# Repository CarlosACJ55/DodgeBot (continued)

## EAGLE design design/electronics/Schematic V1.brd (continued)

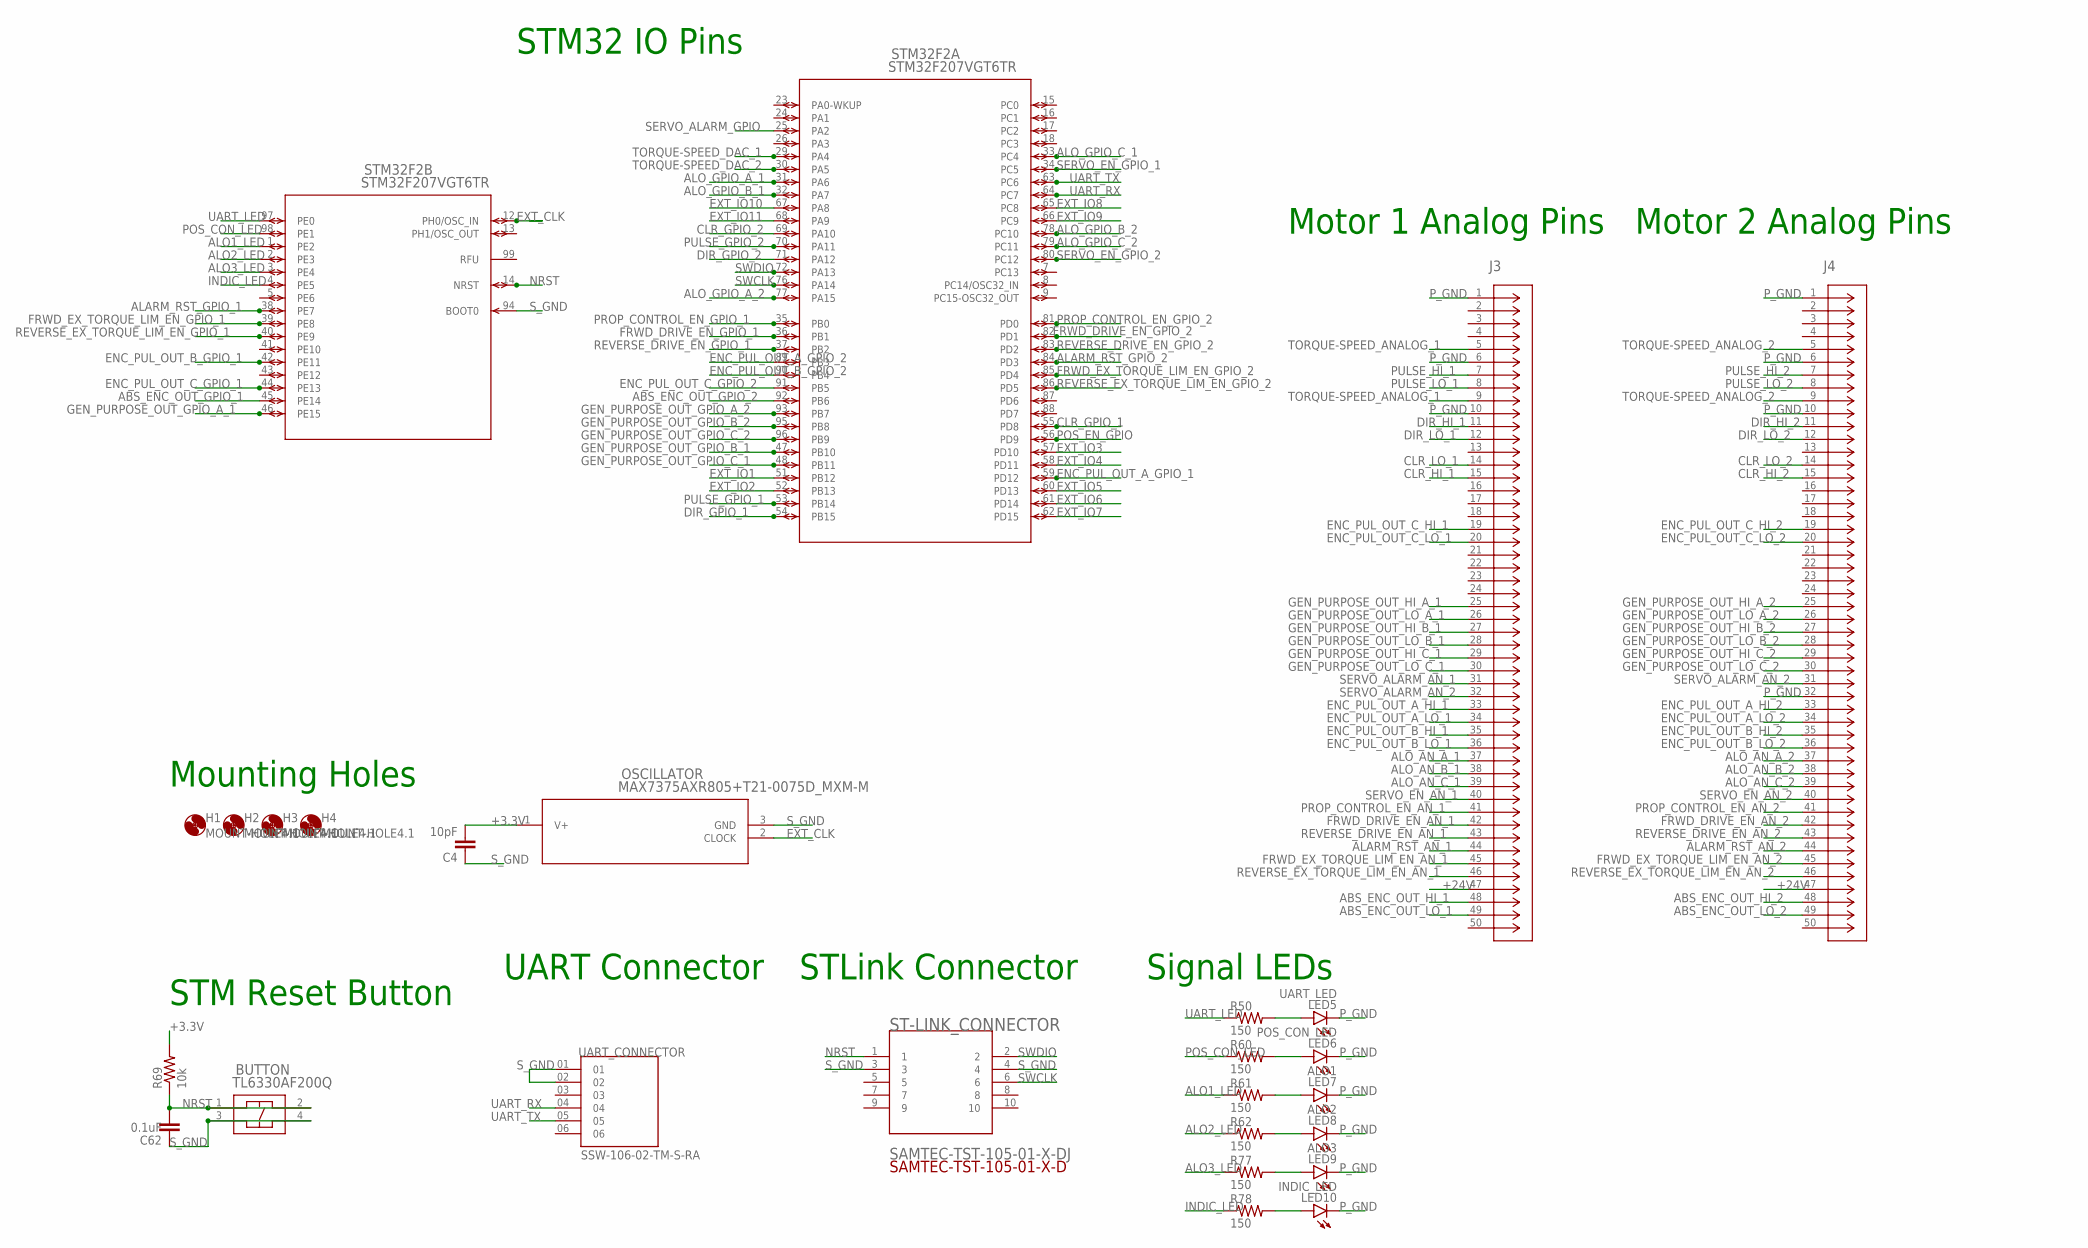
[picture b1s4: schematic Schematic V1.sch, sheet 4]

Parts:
BUTTON: TL6330AF200Q; TL6330_EWI
C4: 10pF; 0805
C62: 0.1uF; 0805
H1, H2, H3, H4: MOUNT-HOLE4.1; 4,1
J3, J4: DD50P564GTXLF; CONN_DD50P564GTXLF_AMP
LED5: UART_LED; CHIPLED_0805
LED6: POS_CON_LED; CHIPLED_0805
LED7: ALO1; CHIPLED_0805
LED8: ALO2; CHIPLED_0805
LED9: ALO3; CHIPLED_0805
LED10: INDIC_LED; CHIPLED_0805
OSCILLATOR: MAX7375AXR805+T21-0075D_MXM-M; 21-0075D_MXM-M
R50, R60, R61, R62, R77, R78: 150; R0805
R69: 10k; R0805
ST-LINK_CONNECTOR: SAMTEC-TST-105-01-X-DJ; SAMTEC-TST-105-01-X-D
STM32F2: STM32F207VGT6TR; LQFP100-14X14MM
UART_CONNECTOR: SSW-106-02-TM-S-RA; SAMTEC_SSW-106-02-TM-S-RA

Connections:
+3.3V: C4.2, OSCILLATOR.1 (V+), R69.2; also elsewhere on the board
+24V: J3.47, J4.47; also elsewhere on the board
ABS_ENC_OUT_GPIO_1: STM32F2.45 (PE14); also elsewhere on the board
ABS_ENC_OUT_GPIO_2: STM32F2.92 (PB6); also elsewhere on the board
ABS_ENC_OUT_HI_1: J3.48; also elsewhere on the board
ABS_ENC_OUT_HI_2: J4.48; also elsewhere on the board
ABS_ENC_OUT_LO_1: J3.49; also elsewhere on the board
ABS_ENC_OUT_LO_2: J4.49; also elsewhere on the board
ALARM_RST_AN_1: J3.44; also elsewhere on the board
ALARM_RST_AN_2: J4.44; also elsewhere on the board
ALARM_RST_GPIO_1: STM32F2.38 (PE7); also elsewhere on the board
ALARM_RST_GPIO_2: STM32F2.84 (PD3); also elsewhere on the board
ALO1_LED: R61.1, STM32F2.1 (PE2)
ALO2_LED: R62.1, STM32F2.2 (PE3)
ALO3_LED: R77.1, STM32F2.3 (PE4)
ALO_AN_A_1: J3.37; also elsewhere on the board
ALO_AN_A_2: J4.37; also elsewhere on the board
ALO_AN_B_1: J3.38; also elsewhere on the board
ALO_AN_B_2: J4.38; also elsewhere on the board
ALO_AN_C_1: J3.39; also elsewhere on the board
ALO_AN_C_2: J4.39; also elsewhere on the board
ALO_GPIO_A_1: STM32F2.31 (PA6); also elsewhere on the board
ALO_GPIO_A_2: STM32F2.77 (PA15); also elsewhere on the board
ALO_GPIO_B_1: STM32F2.32 (PA7); also elsewhere on the board
ALO_GPIO_B_2: STM32F2.78 (PC10); also elsewhere on the board
ALO_GPIO_C_1: STM32F2.33 (PC4); also elsewhere on the board
ALO_GPIO_C_2: STM32F2.79 (PC11); also elsewhere on the board
CLR_GPIO_1: STM32F2.55 (PD8); also elsewhere on the board
CLR_GPIO_2: STM32F2.69 (PA10); also elsewhere on the board
CLR_HI_1: J3.15; also elsewhere on the board
CLR_HI_2: J4.15; also elsewhere on the board
CLR_LO_1: J3.14; also elsewhere on the board
CLR_LO_2: J4.14; also elsewhere on the board
DIR_GPIO_1: STM32F2.54 (PB15); also elsewhere on the board
DIR_GPIO_2: STM32F2.71 (PA12); also elsewhere on the board
DIR_HI_1: J3.11; also elsewhere on the board
DIR_HI_2: J4.11; also elsewhere on the board
DIR_LO_1: J3.12; also elsewhere on the board
DIR_LO_2: J4.12; also elsewhere on the board
ENC_PUL_OUT_A_GPIO_1: STM32F2.59 (PD12); also elsewhere on the board
ENC_PUL_OUT_A_GPIO_2: STM32F2.89 (PB3); also elsewhere on the board
ENC_PUL_OUT_A_HI_1: J3.33; also elsewhere on the board
ENC_PUL_OUT_A_HI_2: J4.33; also elsewhere on the board
ENC_PUL_OUT_A_LO_1: J3.34; also elsewhere on the board
ENC_PUL_OUT_A_LO_2: J4.34; also elsewhere on the board
ENC_PUL_OUT_B_GPIO_1: STM32F2.42 (PE11); also elsewhere on the board
ENC_PUL_OUT_B_GPIO_2: STM32F2.90 (PB4); also elsewhere on the board
ENC_PUL_OUT_B_HI_1: J3.35; also elsewhere on the board
ENC_PUL_OUT_B_HI_2: J4.35; also elsewhere on the board
ENC_PUL_OUT_B_LO_1: J3.36; also elsewhere on the board
ENC_PUL_OUT_B_LO_2: J4.36; also elsewhere on the board
ENC_PUL_OUT_C_GPIO_1: STM32F2.44 (PE13); also elsewhere on the board
ENC_PUL_OUT_C_GPIO_2: STM32F2.91 (PB5); also elsewhere on the board
ENC_PUL_OUT_C_HI_1: J3.19; also elsewhere on the board
ENC_PUL_OUT_C_HI_2: J4.19; also elsewhere on the board
ENC_PUL_OUT_C_LO_1: J3.20; also elsewhere on the board
ENC_PUL_OUT_C_LO_2: J4.20; also elsewhere on the board
EXT_CLK: OSCILLATOR.2 (CLOCK), STM32F2.12 (PH0/OSC_IN)
EXT_IO1: STM32F2.51 (PB12)
EXT_IO2: STM32F2.52 (PB13)
EXT_IO3: STM32F2.57 (PD10)
EXT_IO4: STM32F2.58 (PD11)
EXT_IO5: STM32F2.60 (PD13)
EXT_IO6: STM32F2.61 (PD14)
EXT_IO7: STM32F2.62 (PD15)
EXT_IO8: STM32F2.65 (PC8)
EXT_IO9: STM32F2.66 (PC9)
EXT_IO10: STM32F2.67 (PA8)
EXT_IO11: STM32F2.68 (PA9)
FRWD_DRIVE_EN_AN_1: J3.42; also elsewhere on the board
FRWD_DRIVE_EN_AN_2: J4.42; also elsewhere on the board
FRWD_DRIVE_EN_GPIO_1: STM32F2.36 (PB1); also elsewhere on the board
FRWD_DRIVE_EN_GPIO_2: STM32F2.82 (PD1); also elsewhere on the board
FRWD_EX_TORQUE_LIM_EN_AN_1: J3.45; also elsewhere on the board
FRWD_EX_TORQUE_LIM_EN_AN_2: J4.45; also elsewhere on the board
FRWD_EX_TORQUE_LIM_EN_GPIO_1: STM32F2.39 (PE8); also elsewhere on the board
FRWD_EX_TORQUE_LIM_EN_GPIO_2: STM32F2.85 (PD4); also elsewhere on the board
GEN_PURPOSE_OUT_GPIO_A_1: STM32F2.46 (PE15); also elsewhere on the board
GEN_PURPOSE_OUT_GPIO_A_2: STM32F2.93 (PB7); also elsewhere on the board
GEN_PURPOSE_OUT_GPIO_B_1: STM32F2.47 (PB10); also elsewhere on the board
GEN_PURPOSE_OUT_GPIO_B_2: STM32F2.95 (PB8); also elsewhere on the board
GEN_PURPOSE_OUT_GPIO_C_1: STM32F2.48 (PB11); also elsewhere on the board
GEN_PURPOSE_OUT_GPIO_C_2: STM32F2.96 (PB9); also elsewhere on the board
GEN_PURPOSE_OUT_HI_A_1: J3.25; also elsewhere on the board
GEN_PURPOSE_OUT_HI_A_2: J4.25; also elsewhere on the board
GEN_PURPOSE_OUT_HI_B_1: J3.27; also elsewhere on the board
GEN_PURPOSE_OUT_HI_B_2: J4.27; also elsewhere on the board
GEN_PURPOSE_OUT_HI_C_1: J3.29; also elsewhere on the board
GEN_PURPOSE_OUT_HI_C_2: J4.29; also elsewhere on the board
GEN_PURPOSE_OUT_LO_A_1: J3.26; also elsewhere on the board
GEN_PURPOSE_OUT_LO_A_2: J4.26; also elsewhere on the board
GEN_PURPOSE_OUT_LO_B_1: J3.28; also elsewhere on the board
GEN_PURPOSE_OUT_LO_B_2: J4.28; also elsewhere on the board
GEN_PURPOSE_OUT_LO_C_1: J3.30; also elsewhere on the board
GEN_PURPOSE_OUT_LO_C_2: J4.30; also elsewhere on the board
INDIC_LED: R78.1, STM32F2.4 (PE5)
unnamed: LED5.A, R50.2
unnamed: LED6.A, R60.2
unnamed: LED7.A, R61.2
unnamed: LED8.A, R62.2
unnamed: LED9.A, R77.2
unnamed: LED10.A, R78.2
NRST: BUTTON.1, BUTTON.2, C62.2, R69.1, ST-LINK_CONNECTOR.1, STM32F2.14 (NRST)
POS_CON_LED: R60.1, STM32F2.98 (PE1)
POS_EN_GPIO: STM32F2.56 (PD9); also elsewhere on the board
PROP_CONTROL_EN_AN_1: J3.41; also elsewhere on the board
PROP_CONTROL_EN_AN_2: J4.41; also elsewhere on the board
PROP_CONTROL_EN_GPIO_1: STM32F2.35 (PB0); also elsewhere on the board
PROP_CONTROL_EN_GPIO_2: STM32F2.81 (PD0); also elsewhere on the board
PULSE_GPIO_1: STM32F2.53 (PB14); also elsewhere on the board
PULSE_GPIO_2: STM32F2.70 (PA11); also elsewhere on the board
PULSE_HI_1: J3.7; also elsewhere on the board
PULSE_HI_2: J4.7; also elsewhere on the board
PULSE_LO_1: J3.8; also elsewhere on the board
PULSE_LO_2: J4.8; also elsewhere on the board
P_GND: J3.1, J3.6, J3.10, J4.1, J4.6, J4.10, J4.32, LED5.C, LED6.C, LED7.C, LED8.C, LED9.C, LED10.C; also elsewhere on the board
REVERSE_DRIVE_EN_AN_1: J3.43; also elsewhere on the board
REVERSE_DRIVE_EN_AN_2: J4.43; also elsewhere on the board
REVERSE_DRIVE_EN_GPIO_1: STM32F2.37 (PB2); also elsewhere on the board
REVERSE_DRIVE_EN_GPIO_2: STM32F2.83 (PD2); also elsewhere on the board
REVERSE_EX_TORQUE_LIM_EN_AN_1: J3.46; also elsewhere on the board
REVERSE_EX_TORQUE_LIM_EN_AN_2: J4.46; also elsewhere on the board
REVERSE_EX_TORQUE_LIM_EN_GPIO_1: STM32F2.40 (PE9); also elsewhere on the board
REVERSE_EX_TORQUE_LIM_EN_GPIO_2: STM32F2.86 (PD5); also elsewhere on the board
SERVO_ALARM_AN_1: J3.31; also elsewhere on the board
SERVO_ALARM_AN_2: J3.32, J4.31
SERVO_ALARM_GPIO: STM32F2.25 (PA2); also elsewhere on the board
SERVO_EN_AN_1: J3.40; also elsewhere on the board
SERVO_EN_AN_2: J4.40; also elsewhere on the board
SERVO_EN_GPIO_1: STM32F2.34 (PC5); also elsewhere on the board
SERVO_EN_GPIO_2: STM32F2.80 (PC12); also elsewhere on the board
SWCLK: ST-LINK_CONNECTOR.6, STM32F2.76 (PA14)
SWDIO: ST-LINK_CONNECTOR.2, STM32F2.72 (PA13)
S_GND: BUTTON.3, BUTTON.4, C4.1, C62.1, OSCILLATOR.3 (GND), ST-LINK_CONNECTOR.3, ST-LINK_CONNECTOR.4, STM32F2.94 (BOOT0), UART_CONNECTOR.01, UART_CONNECTOR.02; also elsewhere on the board
TORQUE-SPEED_ANALOG_1: J3.5, J3.9; also elsewhere on the board
TORQUE-SPEED_ANALOG_2: J4.5, J4.9; also elsewhere on the board
TORQUE-SPEED_DAC_1: STM32F2.29 (PA4); also elsewhere on the board
TORQUE-SPEED_DAC_2: STM32F2.30 (PA5); also elsewhere on the board
UART_LED: R50.1, STM32F2.97 (PE0)
UART_RX: STM32F2.64 (PC7), UART_CONNECTOR.04
UART_TX: STM32F2.63 (PC6), UART_CONNECTOR.05

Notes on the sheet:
STM32 IO Pins
Motor 1 Analog Pins
STLink Connector
UART Connector
STM Reset Button
Motor 2 Analog Pins
Mounting Holes
Signal LEDs

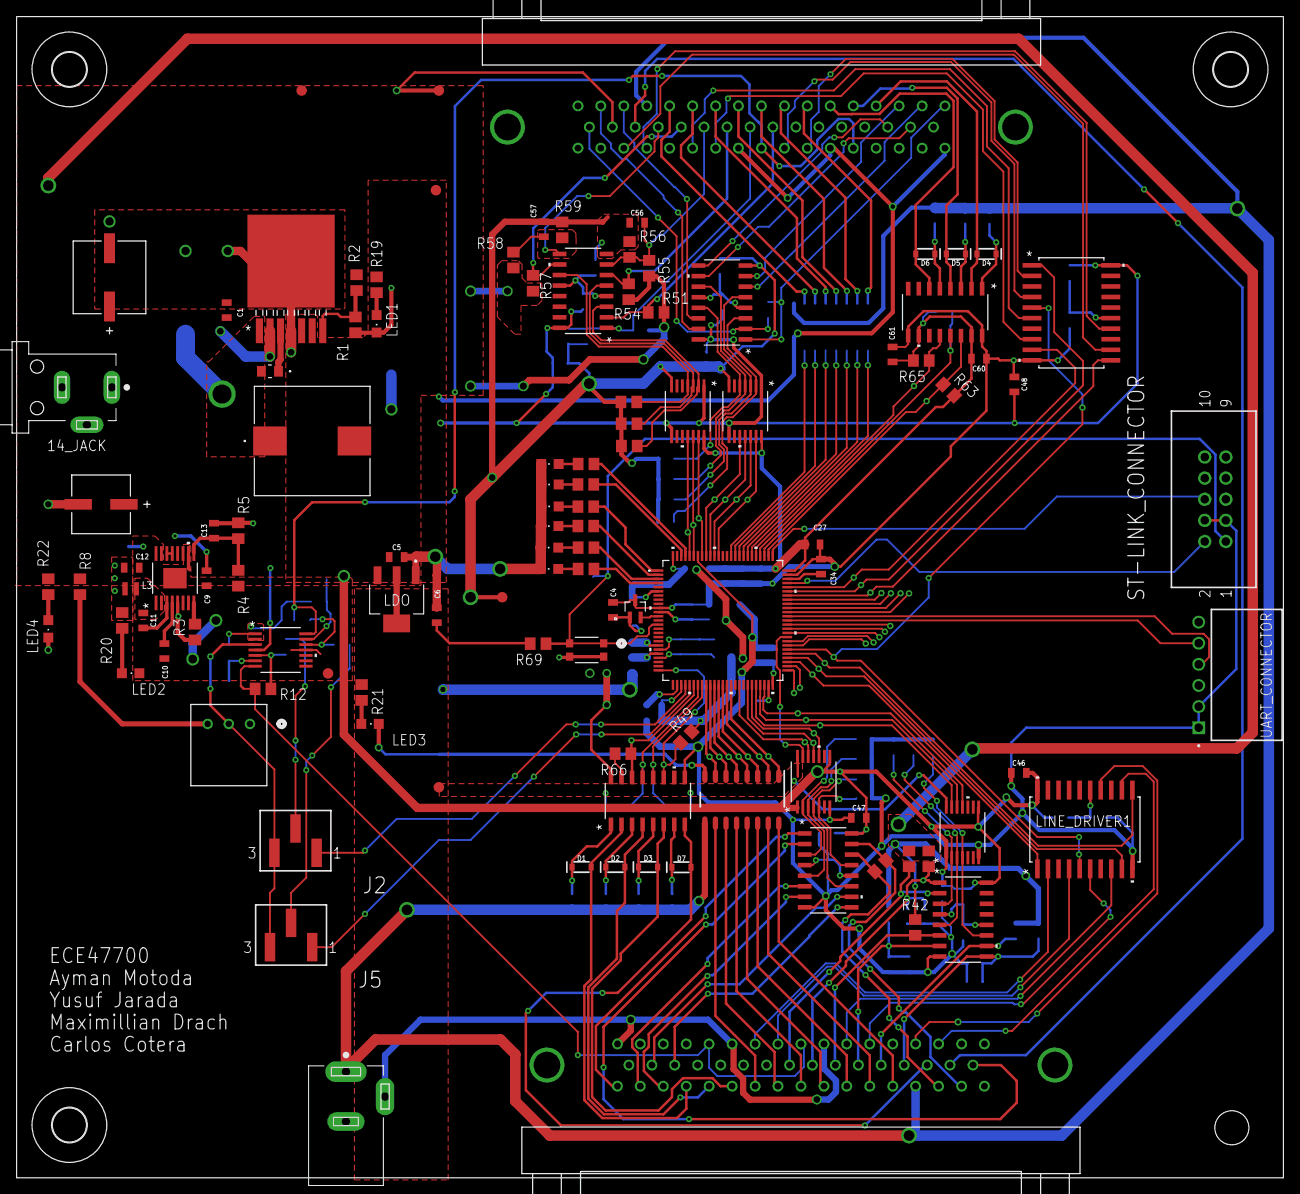
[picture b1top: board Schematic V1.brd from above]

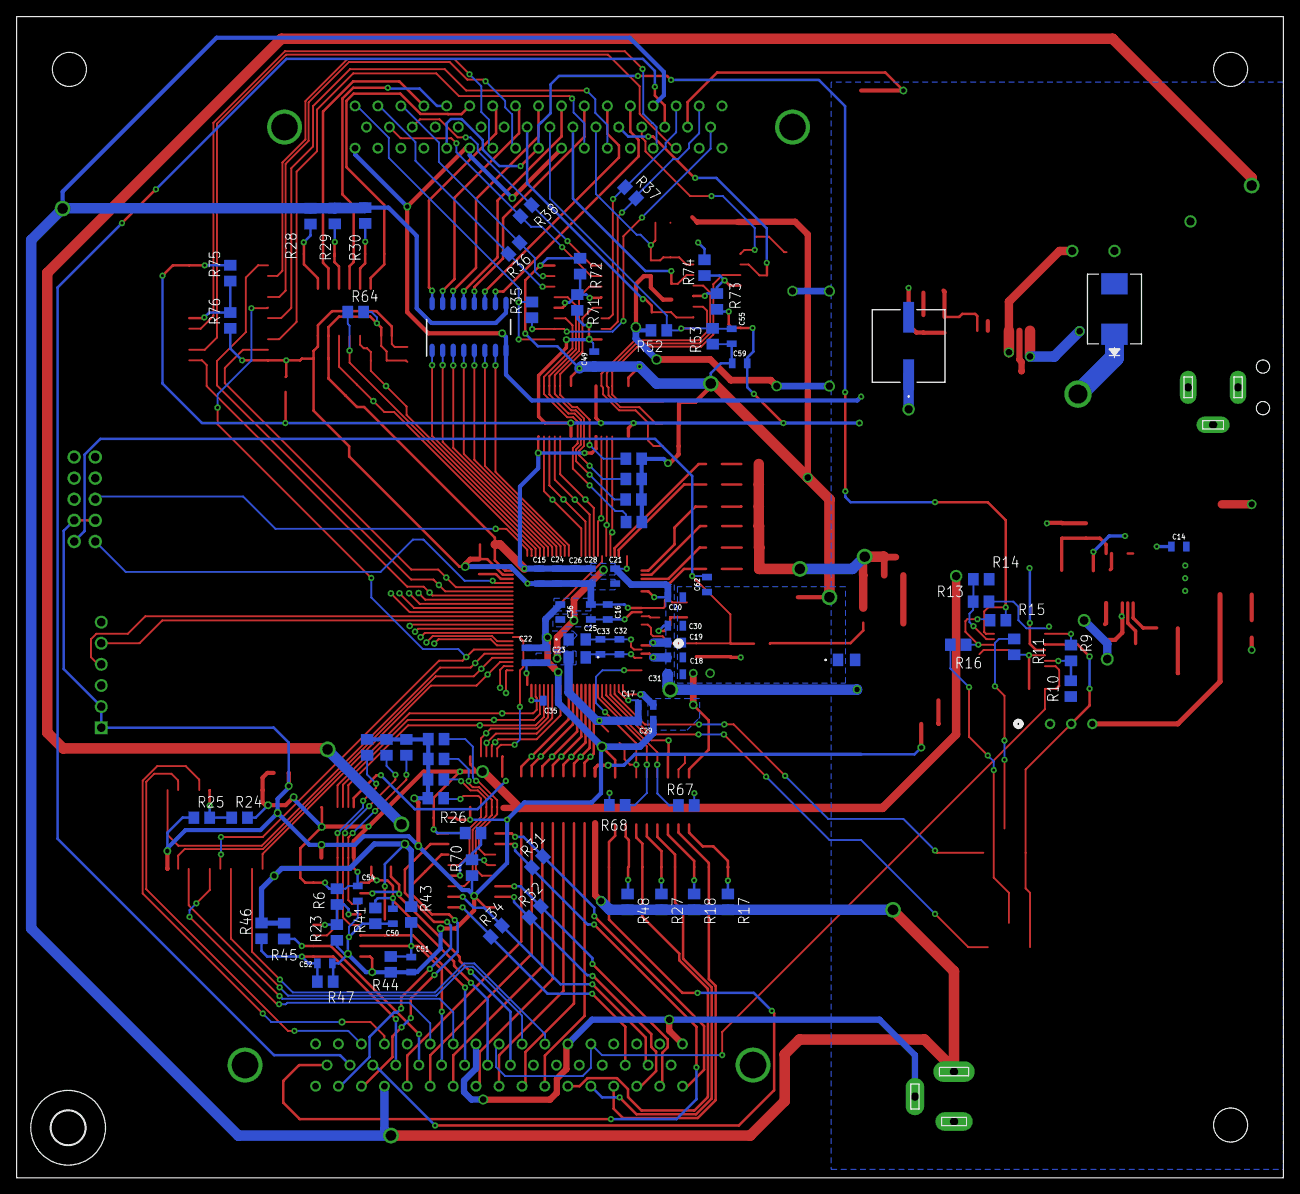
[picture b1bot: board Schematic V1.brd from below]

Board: 2 copper layers, 152.4 x 139.7 mm, 205 parts (91 on the bottom side), 185 nets.

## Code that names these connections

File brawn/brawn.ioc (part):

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Mcu.Name=STM32F207V(C-E-F-G)Tx
Mcu.Package=LQFP100
Mcu.UserName=STM32F207VGTx
PA10.GPIOParameters=GPIO_Label
PA10.GPIO_Label=CLR_GPIO_2
PA10.Signal=GPIO_Output
PA11.GPIOParameters=GPIO_Label
PA11.GPIO_Label=PULSE_GPIO_2
PA11.Signal=S_TIM1_CH4
PA12.GPIOParameters=GPIO_Label
PA12.GPIO_Label=DIR_GPIO_2
PA12.Signal=GPIO_Output
PA13.Mode=Serial_Wire
PA13.Signal=SYS_JTMS-SWDIO
PA14.Mode=Serial_Wire
PA14.Signal=SYS_JTCK-SWCLK
PA15.GPIOParameters=GPIO_Label
PA15.GPIO_Label=ALO_GPIO_A_2
PA15.Signal=GPIO_Input
PA2.GPIOParameters=GPIO_Label
PA2.GPIO_Label=ALARM_NOTIF
PA2.Signal=GPXTI2
PA4.Signal=COMP_DAC1_group
PA5.Signal=COMP_DAC2_group
PA6.GPIOParameters=GPIO_Label
PA6.GPIO_Label=ALO_GPIO_A_1
PA6.Signal=GPIO_Input
PA7.GPIOParameters=GPIO_Label
PA7.GPIO_Label=ALO_GPIO_B_1
PA7.Signal=GPIO_Input
PB0.GPIOParameters=GPIO_Label
PB0.GPIO_Label=PROP_CONTROL_EN_GPIO_1
PB0.Signal=GPIO_Output
PB1.GPIOParameters=GPIO_Label
PB1.GPIO_Label=FRWD_DRIVE_EN_GPIO_1
PB1.Signal=GPIO_Output
PB10.GPIOParameters=GPIO_Label
PB10.GPIO_Label=GEN_PURPOSE_OUT_GPIO_B_1
PB10.Signal=GPIO_Input
PB11.GPIOParameters=GPIO_Label
PB11.GPIO_Label=GEN_PURPOSE_OUT_GPIO_C_1
PB11.Signal=GPIO_Input
PB14.GPIOParameters=GPIO_Label
PB14.GPIO_Label=PULSE_GPIO_1
PB14.Signal=S_TIM12_CH1
PB15.GPIOParameters=GPIO_Label
PB15.GPIO_Label=DIR_GPIO_1
PB15.Signal=GPIO_Output
PB2.GPIOParameters=GPIO_Label
PB2.GPIO_Label=REVERSE_DRIVE_EN_GPIO_1
PB2.Signal=GPIO_Output
PB3.GPIOParameters=GPIO_Label
PB3.GPIO_Label=ENC_A_GPIO_2
PB3.Signal=GPIO_Input
PB4.GPIOParameters=GPIO_Label
PB4.GPIO_Label=ENC_B_GPIO_2
PB4.Signal=GPIO_Input
PB5.GPIOParameters=GPIO_Label
PB5.GPIO_Label=ENC_C_GPIO_2
PB5.Signal=GPIO_Input
PB6.GPIOParameters=GPIO_Label
PB6.GPIO_Label=ABS_ENC_GPIO_2
PB6.Signal=GPIO_Input
PB7.GPIOParameters=GPIO_Label
PB7.GPIO_Label=GEN_PURPOSE_OUT_GPIO_A_2
PB7.Signal=GPIO_Input
PB8.GPIOParameters=GPIO_Label
PB8.GPIO_Label=GEN_PURPOSE_OUT_GPIO_B_2
PB8.Signal=GPIO_Input
PB9.GPIOParameters=GPIO_Label
PB9.GPIO_Label=GEN_PURPOSE_OUT_GPIO_C_2
PB9.Signal=GPIO_Input
PC10.GPIOParameters=GPIO_Label
PC10.GPIO_Label=ALO_GPIO_B_2
PC10.Signal=GPIO_Input
PC11.GPIOParameters=GPIO_Label
PC11.GPIO_Label=ALO_GPIO_C_2
PC11.Signal=GPIO_Input
PC12.GPIOParameters=GPIO_Label
PC12.GPIO_Label=SERVO_EN_GPIO_2
PC12.Signal=GPIO_Output
PC4.GPIOParameters=GPIO_Label
PC4.GPIO_Label=ALO_GPIO_C_1
PC4.Signal=GPIO_Input
PC5.GPIOParameters=GPIO_Label
PC5.GPIO_Label=SERVO_EN_GPIO_1
PC5.Signal=GPIO_Output
PC6.Mode=Asynchronous
PC6.Signal=USART6_TX
PC7.Mode=Asynchronous
PC7.Signal=USART6_RX
PD0.GPIOParameters=GPIO_Label
PD0.GPIO_Label=PROP_CONTROL_EN_GPIO_2
PD0.Signal=GPIO_Output
PD1.GPIOParameters=GPIO_Label
PD1.GPIO_Label=FRWD_DRIVE_EN_GPIO_2
PD1.Signal=GPIO_Output
PD12.GPIOParameters=GPIO_Label
PD12.GPIO_Label=ENC_A_GPIO_1
PD12.Signal=GPIO_Input
PD2.GPIOParameters=GPIO_Label
PD2.GPIO_Label=REVERSE_DRIVE_EN_GPIO_2
PD2.Signal=GPIO_Output
PD3.GPIOParameters=GPIO_Label
PD3.GPIO_Label=ALARM_RST_GPIO_2
PD3.Signal=GPIO_Output
PD4.GPIOParameters=GPIO_Label
PD4.GPIO_Label=FRWD_EXT_TORQUE_LIM_EN_GPIO_2
PD4.Signal=GPIO_Output
PD5.GPIOParameters=GPIO_Label
PD5.GPIO_Label=REVERSE_EXT_TORQUE_LIM_EN_GPIO_2
PD5.Signal=GPIO_Output
PD8.GPIOParameters=GPIO_Label
PD8.GPIO_Label=CLR_GPIO_1
PD8.Signal=GPIO_Output
PD9.GPIOParameters=PinState,GPIO_Label
PD9.GPIO_Label=POS_EN_GPIO
PD9.PinState=GPIO_PIN_SET
PD9.Signal=GPIO_Output
PE0.GPIOParameters=GPIO_Label
PE0.GPIO_Label=ALO1_LED_A
PE0.Signal=GPIO_Output
PE1.GPIOParameters=GPIO_Label
PE1.GPIO_Label=ALO1_LED_B
PE1.Signal=GPIO_Output
PE11.GPIOParameters=GPIO_Label
PE11.GPIO_Label=ENC_B_GPIO_1
PE11.Signal=GPIO_Input
PE13.GPIOParameters=GPIO_Label
PE13.GPIO_Label=ENC_C_GPIO_1
PE13.Signal=GPIO_Input
PE14.GPIOParameters=GPIO_Label
PE14.GPIO_Label=ABS_ENC_GPIO_1
PE14.Signal=GPIO_Input
PE15.GPIOParameters=GPIO_Label
PE15.GPIO_Label=GEN_PURPOSE_OUT_GPIO_A_1
PE15.Signal=GPIO_Input
PE2.GPIOParameters=GPIO_Label
PE2.GPIO_Label=ALO1_LED_C
PE2.Signal=GPIO_Output
PE3.GPIOParameters=GPIO_Label
PE3.GPIO_Label=ALO2_LED_A
PE3.Signal=GPIO_Output
PE4.GPIOParameters=GPIO_Label
PE4.GPIO_Label=ALO2_LED_B
PE4.Signal=GPIO_Output
PE5.GPIOParameters=GPIO_Label
PE5.GPIO_Label=ALO2_LED_C
PE5.Signal=GPIO_Output
PE7.GPIOParameters=GPIO_Label
PE7.GPIO_Label=ALARM_RST_GPIO_1
PE7.Signal=GPIO_Output
PE8.GPIOParameters=GPIO_Label
PE8.GPIO_Label=FRWD_EXT_TORQUE_LIM_EN_GPIO_1
PE8.Signal=GPIO_Output
PE9.GPIOParameters=GPIO_Label
PE9.GPIO_Label=REVERSE_EXT_TORQUE_LIM_EN_GPIO_1
PE9.Signal=GPIO_Output
PH0-OSC_IN.Mode=HSE-External-Oscillator
PH0-OSC_IN.Signal=RCC_OSC_IN
PH1-OSC_OUT.Mode=HSE-External-Oscillator
PH1-OSC_OUT.Signal=RCC_OSC_OUT
RCC.HSE_VALUE=25000000
RCC.SYSCLKFreq_VALUE=120000000
RCC.SYSCLKSource=RCC_SYSCLKSOURCE_PLLCLK
board=custom

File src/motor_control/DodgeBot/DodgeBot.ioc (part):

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Mcu.Name=STM32F746ZGTx
Mcu.Package=LQFP144
Mcu.UserName=STM32F746ZGTx
PA10.GPIOParameters=GPIO_Label
PA10.GPIO_Label=CLR_GPIO_2
PA10.Signal=GPIO_Output
PA11.GPIOParameters=GPIO_Label
PA11.GPIO_Label=PULSE_GPIO_2
PA11.Signal=GPIO_Output
PA12.GPIOParameters=GPIO_Label
PA12.GPIO_Label=DIR_GPIO_2
PA12.Signal=GPIO_Output
PA13.Signal=SYS_JTMS-SWDIO
PA14.Signal=SYS_JTCK-SWCLK
PA15.GPIOParameters=GPIO_Label
PA15.GPIO_Label=ALO_GPIO_A_2
PA15.Signal=GPIO_Input
PA4.GPIOParameters=GPIO_Label
PA4.GPIO_Label=TORQUE-SPEED_DAC_1
PA4.Signal=COMP_DAC1_group
PA5.GPIOParameters=GPIO_Label
PA5.GPIO_Label=TORQUE-SPEED_DAC_2
PA5.Signal=COMP_DAC2_group
PA6.GPIOParameters=GPIO_Label
PA6.GPIO_Label=ALO_GPIO_A_1
PA6.Signal=GPIO_Input
PA7.GPIOParameters=GPIO_Label
PA7.GPIO_Label=ALO_GPIO_B_1
PA7.Signal=GPIO_Input
PB0.GPIOParameters=GPIO_Label
PB0.GPIO_Label=PRP_CNTRL_EN_GPIO_1
PB0.Signal=GPIO_Output
PB1.GPIOParameters=GPIO_Label
PB1.GPIO_Label=FWD_DRIVE_EN_GPIO_1
PB1.Signal=GPIO_Output
PB10.GPIOParameters=GPIO_Label
PB10.GPIO_Label=GEN_PURPOSE_OUT_GPIO_C_1
PB10.Signal=GPIO_Input
PB11.GPIOParameters=GPIO_Label
PB11.GPIO_Label=SERVO_ALARM_OUT_GPIO_1
PB11.Signal=GPIO_Input
PB13.GPIOParameters=GPIO_Label
PB13.GPIO_Label=PULSE_GPIO_1
PB13.Signal=GPIO_Output
PB14.GPIOParameters=GPIO_Label
PB14.GPIO_Label=DIR_GPIO_1
PB14.Signal=GPIO_Output
PB15.GPIOParameters=GPIO_Label
PB15.GPIO_Label=CLR_GPIO_1
PB15.Signal=GPIO_Output
PB2.GPIOParameters=GPIO_Label
PB2.GPIO_Label=REV_DRIVE_EN_GPIO_1
PB2.Signal=GPIO_Output
PB3.GPIOParameters=GPIO_Label
PB3.GPIO_Label=ENC_PUL_OUT_C_GPIO_2
PB3.Signal=GPIO_Input
PB4.GPIOParameters=GPIO_Label
PB4.GPIO_Label=ABS_ENC_OUT_GPIO_2
PB4.Signal=GPIO_Input
PB5.GPIOParameters=GPIO_Label
PB5.GPIO_Label=GEN_PURPOSE_OUT_GPIO_A_2
PB5.Signal=GPIO_Input
PB6.GPIOParameters=GPIO_Label
PB6.GPIO_Label=GEN_PURPOSE_OUT_GPIO_B_2
PB6.Signal=GPIO_Input
PB7.GPIOParameters=GPIO_Label
PB7.GPIO_Label=GEN_PURPOSE_OUT_GPIO_C_2
PB7.Signal=GPIO_Input
PB8.GPIOParameters=GPIO_Label
PB8.GPIO_Label=SERVO_ALARM_OUT_GPIO_2
PB8.Signal=GPIO_Input
PC10.GPIOParameters=GPIO_Label
PC10.GPIO_Label=ALO_GPIO_B_2
PC10.Signal=GPIO_Input
PC11.GPIOParameters=GPIO_Label
PC11.GPIO_Label=ALO_GPIO_C_2
PC11.Signal=GPIO_Input
PC12.GPIOParameters=GPIO_Label
PC12.GPIO_Label=SERVO_EN_GPIO_2
PC12.Signal=GPIO_Output
PC4.GPIOParameters=GPIO_Label
PC4.GPIO_Label=ALO_GPIO_C_1
PC4.Signal=GPIO_Input
PC5.GPIOParameters=GPIO_Label
PC5.GPIO_Label=SERVO_EN_GPIO_1
PC5.Signal=GPIO_Output
PC6.GPIOParameters=GPIO_Label
PC6.GPIO_Label=UART_TX
PC6.Signal=GPIO_Input
PC7.GPIOParameters=GPIO_Label
PC7.GPIO_Label=UART_RX
PC7.Signal=GPXTI7
PD0.GPIOParameters=GPIO_Label
PD0.GPIO_Label=PROP_CONROL_EN_GPIO_2
PD0.Signal=GPIO_Output
PD1.GPIOParameters=GPIO_Label
PD1.GPIO_Label=FWD_DRIVE_EN_GPIO_2
PD1.Signal=GPIO_Output
PD2.GPIOParameters=GPIO_Label
PD2.GPIO_Label=REV_DRIVE_EN_GPIO_2
PD2.Signal=GPIO_Output
PD3.GPIOParameters=GPIO_Label
PD3.GPIO_Label=ALARM_RST_GPIO_2
PD3.Signal=GPIO_Output
PD4.GPIOParameters=GPIO_Label
PD4.GPIO_Label=FWD_EX_TORQUE_LIM_EN_GPIO_2
PD4.Signal=GPIO_Output
PD5.GPIOParameters=GPIO_Label
PD5.GPIO_Label=REV_EX_TORQUE_LIM_EN_GPIO_2
PD5.Signal=GPIO_Output
PD6.GPIOParameters=GPIO_Label
PD6.GPIO_Label=ENC_PUL_OUT_A_GPIO_2
PD6.Signal=GPIO_Input
PD7.GPIOParameters=GPIO_Label
PD7.GPIO_Label=ENC_PUL_OUT_B_GPIO_2
PD7.Signal=GPIO_Input
PD8.GPIOParameters=GPIO_Label
PD8.GPIO_Label=POS_EN_GPIO
PD8.Signal=GPIO_Output
PE10.GPIOParameters=GPIO_Label
PE10.GPIO_Label=ENC_PUL_OUT_A_GPIO_1
PE10.Signal=GPIO_Input
PE11.GPIOParameters=GPIO_Label
PE11.GPIO_Label=ENC_PUL_OUT_B_GPIO_1
PE11.Signal=GPIO_Input
PE12.GPIOParameters=GPIO_Label
PE12.GPIO_Label=ENC_PUL_OUT_C_GPIO_1
PE12.Signal=GPIO_Input
PE13.GPIOParameters=GPIO_Label
PE13.GPIO_Label=ABS_ENC_OUT_GPIO_1
PE13.Signal=GPIO_Input
PE14.GPIOParameters=GPIO_Label
PE14.GPIO_Label=GEN_PURPOSE_OUT_GPIO_A_1
PE14.Signal=GPIO_Input
PE15.GPIOParameters=GPIO_Label
PE15.GPIO_Label=GEN_PURPOSE_OUT_GPIO_B_1
PE15.Signal=GPIO_Input
PE7.GPIOParameters=GPIO_Label
PE7.GPIO_Label=ALARM_RST_EN_GPIO_1
PE7.Signal=GPIO_Output
PE8.GPIOParameters=GPIO_Label
PE8.GPIO_Label=FWD_EX_TORQUE_LIM_EN_GPIO_2
PE8.Signal=GPIO_Output
PE9.GPIOParameters=GPIO_Label
PE9.GPIO_Label=REV_EX_TORQUE_LIM_EN_GPIO_1
PE9.Signal=GPIO_Output
PH0/OSC_IN.GPIOParameters=GPIO_Label
PH0/OSC_IN.GPIO_Label=EXT_CLK
PH0/OSC_IN.Signal=GPIO_Input
RCC.HSE_VALUE=26000000
RCC.SYSCLKFreq_VALUE=108000000
RCC.SYSCLKSource=RCC_SYSCLKSOURCE_PLLCLK
board=custom

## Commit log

2024-01-09 this is commit
2024-01-09 Initial website commit + gitignore
2024-01-09 Modified team specific tags on the website.
2024-01-09 Added the link to the group website.
2024-01-11 Added Files
2024-01-11 docs
2024-01-11 added files for camera test
2024-01-11 updated template and color code
2024-01-11 Website is up.
2024-01-11 Final Project Proposal: completed price estimate
2024-01-12 PSNRs
2024-01-12 Updated A1
2024-01-12 Updated the A1 with power & motor PSDRs
2024-01-12 a1 changes
2024-01-12 clean up
2024-01-13 a1 max
2024-01-13 max a1
2024-01-13 Simulation of both scenarios
2024-01-13 reformat
2024-01-13 removed comments from document
2024-01-14 Added CAD FOLDER
2024-01-14 Started working on CAD
2024-01-16 Added STM & Motor Spin Files
2024-01-16 Added CAD FILES AND EAGLE FILES
2024-01-16 updated website
2024-01-17 Updated SpinningMotor Calculation
2024-01-20 Motor Calculation Updated
2024-01-20 Updated Labels on Graphs
2024-01-20 Updated Motor
2024-01-20 Updated Motor Configuration
2024-01-21 Finished A2
2024-01-21 Added A2
2024-01-21 Fixed Naming of Doc
2024-01-21 Readded A1
2024-01-23 camera update
2024-01-23 folder update
2024-01-23 reorganizing
2024-01-23 Updated STM32 Code for F7
2024-01-23 double punch code
2024-01-23 cam update
2024-01-23 worked on STM Code
2024-01-23 punch dodging draft demo
2024-01-24 Added BOM File & Updated Schematic
2024-01-25 STM COde
2024-01-25 Cleaned up STM CODE
2024-01-26 camera tracking update
2024-01-26 camera optimization
2024-01-27 reorganized MATLAB files
2024-01-28 completed A3
2024-01-30 camera calibration code
2024-01-30 updated website code
2024-01-30 clean uo git
2024-01-30 merged python files
2024-01-30 updated gitignore
2024-02-01 updates to kmeans for higher efficienticies
2024-02-01 Added A4 + Updated Schematic
2024-02-02 simple changes to cam test
2024-02-02 camera updates
2024-02-02 added in the avrg compute time
2024-02-03 Updated Simulation Files with Updated Motor Values
2024-02-03 Updated Image Names
2024-02-04 Uploaded finished A5
2024-02-06 CAD and STM CODE
    sorry for massive push
2024-02-06 camera updates
    change bug in the avoidance where it was reading the x&y
2024-02-06 camera changes
2024-02-07 Updated Motor File for New Setup
2024-02-07 Added CAD files
2024-02-08 finished up CAD
2024-02-08 STM CODE HAS BEEN REMOVED
    I will make a new folder
2024-02-08 CAD ALMOST DONE
2024-02-08 Updated Schematic with Main Features
2024-02-09 robot camera mapping
2024-02-10 tracking optimization
2024-02-10 fixed the constraint issue with assembly
2024-02-10 re-structured repository
2024-02-11 Updated Schematic
2024-02-11 Updated Library and BOM
2024-02-11 Finished Schematics, Libraries, and BOM
2024-02-11 Updated BOM with Prices
2024-02-11 Created board layout, updated schematic on Buck Capacitors, Updated BOM, Updated Library
2024-02-12 updated website content
2024-02-12 removed website from repository
2024-02-13 new stm project and basic ui started
2024-02-13 added parts
2024-02-13 Bossed Up on the CAD
2024-02-13 more
2024-02-14 new camera mapping function
2024-02-14 Updated Schematic, board layout, BOM, and libraries
2024-02-14 Updated layout parts
2024-02-15 Updated Power Circuit Schematic + Layout + Components
2024-02-15 Updated Schematic and Board with a few components
2024-02-15 Updated BOM with updated part quantities
2024-02-16 Updated Power Scheme of STM32
2024-02-16 Purchase Order Forms Added
2024-02-17 Updated Schematic Layout
2024-02-17 Updated Layout with most ICs on board now
2024-02-18 More of the layout is added
2024-02-20 Updated Layout with most traces
2024-02-20 Moved UART signals to different pins for routing.
2024-02-20 name changes & updates
2024-02-20 new indenting
2024-02-20 did one singular pin and im failing
2024-02-20 CAD progress
2024-02-21 Updated schematic, added amazon order purchase
2024-02-21 Updated Layout more
2024-02-22 Layout almost done
2024-02-23 Yay it's hooked up
2024-02-23 Added DRC checker
2024-02-26 Updated part library of barrel jack + stretched polygons
2024-02-27 Updated PCB Connector Placement
2024-02-27 Fixed traces
2024-02-27 Updated Layout
2024-02-27 Completed pin setup for DodgeBot STM32F7 test chip
2024-02-27 cad stuff
2024-02-27 Finished PCB
2024-02-28 Moved 2-frame page to separate page
2024-02-28 Adding VIAs to STM traces
2024-02-28 cad update
2024-02-28 camera minor adjustments
2024-02-28 Updated Labels + Finished PCB
2024-03-07 Added Traces
2024-03-07 Added jumper connectors to DAC input, added EXT IO Pins
2024-03-07 Finished Design
2024-03-08 Added pull downs to level shifter 5V lines
2024-03-08 Gerber Files Uploaded
2024-03-09 Updated silkscreen and trace error
2024-03-09 Fixed Silkscreen cover over EXT_GPIO Pins
2024-03-18 serial code
2024-03-22 Full stack skeleton design for game
2024-03-23 Copied in computer vision code
2024-03-25 Added file ignoring and developped sentry.py
2024-03-25 Improved README.md and organized documentation
2024-03-26 Created an abstract message.py class. Safely implements the string manipulation logic for messages transmitted over UART
2024-03-27 Communication protocol design initial implementation complete
2024-03-27 added stm32 actuation package
    The stm config is correct here
2024-03-27 quick fixes
2024-03-27 ignoring clion files
2024-03-28 Initial draft for stm implementation
2024-03-28 Fixed imports
2024-03-29 de-bugged first draft main.c on school computer
    -Carlos
2024-03-29 Created unit tests
2024-03-31 Variable length transmission is perfect
2024-03-31 Removed parity for manual check
2024-03-31 Added A10 to Respository
2024-03-31 Cleaned old nucleo.ioc folder
2024-03-31 activated advanced it receive interrupt
2024-04-01 All connection.py tests passed
    Fully implemented communications protocol to encode and decode duplicated messages between python and stm with miniscule chance of packet loss in either direction.
2024-04-01 Testing protocol.py.
    Sync command test passing, other commands failing.
2024-04-01 Implemented initial game logic
    handled both Command and Move type messages and implemented a move queue to de-bounce Move instructions. Not tested
    Author: Carlos
2024-04-01 Redesigned protocol.py, cleaned stm code.
2024-04-02 Improved move message handling
    not passing all protocol tests yet!
    -Carlos
2024-04-02 Improved move message tests, not all passing yet
2024-04-02 Completed tst/protocol.py file
    Now, going to work on actuation stm code to make all tests pass
2024-04-02 Formalized ECHO mode
2024-04-02 ALL protocol.py TESTS PASSED!!!!!
2024-04-02 All PROTOCOL TESTS PASSED!
    Movement and game states accurately and efficiently tracked
2024-04-02 Small efficiency debug
2024-04-02 Cleared repo to reorganize with poetry and git commands.
2024-04-02 "Cleared repo to reorganize with poetry and git commands."
    Random DS Store file popped up
2024-04-02 Create README.md
    Included basic info and status icon
2024-04-02 Initial gitignore to avoid DS Store files
2024-04-02 Added motor models to README.md
2024-04-02 Uploaded documentation.
2024-04-02 Update README.md
    Reformatted dependencies
2024-04-02 Fixed Readme.md bolding
2024-04-02 Updated gitignore.
2024-04-02 Added connection and protocol packages. Implemented testing and automated GitHub tools checking.
2024-04-02 Implemented vision and game logic
2024-04-03 Added GUI and calibration files, initialized testing suite
2024-04-03 Started debugging gui and game
2024-04-03 Fixed dependencies
2024-04-03 Fixed yaml
2024-04-03 Fixed yaml again.
2024-04-03 Fixed yaml again again.
2024-04-03 Fixed yaml again again again.
2024-04-03 Fixed pyproject.toml
2024-04-03 Fixed python-app.yml again
2024-04-03 Reinserted STM code
2024-04-03 renamed actuation to brawn and cleaned ioc and build
2024-04-03 Improved gitignore to ignore non essential stmcubemx generated files
    Anything in the ioc and stm code before pressing build still included
2024-04-03 improved venv gitignore and started game tests
2024-04-03 Created Simulation mode for testing full game without motors
    also cleaned some gitignorable files
2024-04-04 Improved game
2024-04-04 fixed typo in test_game.py
2024-04-04 update to the pathfinder file
2024-04-04 Added 4/6 gpio input configurations from servo
    -Carlos
2024-04-05 pathfinder updates
2024-04-07 Completed Ethical and Environmental analysis.
2024-04-08 Partially de-bugged UI and game
    Author: Carlos
    Started integration tests between Pathfinder and Game. This commit is decent enough to allow Max to commence proper testing and improvements of the pathfinder class
2024-04-08 Initial draft for SIM
    Author: Carlos
    SIM is a new build configuration I added to enable full integration testing of game.py and pathfinder.py without the need for motor connenection
2024-04-09 First functional Integration test working!
2024-04-09 First functional integration test passing!
2024-04-11 Fixed Tkinter concurrency issue where timer was blocking UI.
2024-04-11 height constant updates
2024-04-15 camera tracking for robot tracking updates
2024-04-18 stm changes
2024-04-18 game state changes,
    fixed threading issues, also some issues with one punch detection
2024-04-24 final code sumbit
2024-04-28 all mechincal designs
2024-04-28 small updates
2024-09-10 new video
2024-09-10 video change
